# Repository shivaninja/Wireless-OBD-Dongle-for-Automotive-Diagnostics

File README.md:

# Wireless OBD Dongle for Automotive Diagnostics

A custom ESP32-based wireless OBD-II dongle designed to interface with a vehicle's diagnostic port and provide a hardware platform for automotive data acquisition and diagnostics.

This repository currently contains the **KiCad hardware design**: the schematic, PCB layout, supporting symbol/footprint libraries, and 3D component models.

## Project overview

The board is built around an **ESP32-WROOM-32E** module and a **TCAN332 CAN transceiver**. The OBD-II connector provides the vehicle-side interface, while the ESP32 provides the processing and wireless-capable platform.

The design also includes a vehicle-input power conversion stage, USB connectivity for development/programming, user push-buttons, and status LEDs.

> **Repository scope:** The uploaded project contains hardware design files. It does not currently include ESP32 firmware, a mobile application, or a PC diagnostic application. Therefore, software features and supported OBD-II diagnostic parameters depend on firmware and host software that are developed separately.

## Main hardware

| Component / circuit | Purpose |
|---|---|
| ESP32-WROOM-32E | Main microcontroller and wireless-capable processing module |
| TCAN332 | CAN bus physical-layer transceiver |
| C-OBD-II-16M | OBD-II vehicle connector |
| TPS62162DSG | Step-down DC/DC regulator in the power supply section |
| CH340C | USB-to-UART interface |
| USB-C receptacle | USB connection for development / serial communication |
| USBLC6-4SC6 | USB line protection |
| PESD2CANFD24V-T | CAN bus transient/ESD protection |
| SS8050 | NPN transistor used in the supporting circuitry |
| LEDs and push-buttons | Board indication and user input |

Refer to the schematic for the exact wiring, component values, and pin assignments.

## Hardware design

### Schematic

The schematic contains the ESP32 section, CAN transceiver and protection, OBD-II connector, power regulation, USB-to-UART interface, and supporting user-interface circuitry.

### PCB layout

The PCB design includes front- and back-copper routing.

**Front copper**

**Back copper**

### 3D board views

## How the hardware is intended to work

1. The dongle plugs into the vehicle's OBD-II diagnostic connector.
2. The power-supply stage converts the vehicle-side input to a regulated supply for the board.
3. The ESP32 acts as the main controller.
4. The TCAN332 interfaces the controller's CAN signals with the vehicle CAN bus at the physical layer.
5. The ESP32 can use its wireless capabilities to communicate with a separate diagnostic client once suitable firmware and client software are implemented.

The CAN transceiver is the physical-layer interface; OBD-II request/response handling, CAN message processing, wireless data transport, and diagnostic display require software.

## Repository contents

```text
.
├── ESP-CAN.kicad_sch          # KiCad schematic
├── ESP-CAN.kicad_pcb          # KiCad PCB layout
├── ESP-CAN.kicad_pro          # KiCad project settings
├── Pictures/                  # Schematic, PCB, 3D and design-check images
├── C-OBD-II-16M/              # OBD-II connector symbol, footprint and 3D model
├── TCAN332-3D-Model/          # CAN transceiver 3D model
├── TPS62162DSGR-3D-Model/     # Regulator 3D model
├── USB-3d-Model/              # USB connector 3D model
├── fp-lib-table               # KiCad footprint library table
└── sym-lib-table              # KiCad symbol library table
```

## Opening the design

1. Install [KiCad](https://www.kicad.org/).
2. Clone or download this repository.
3. Open `ESP-CAN.kicad_pro` in KiCad.
4. Open the schematic (`ESP-CAN.kicad_sch`) or PCB editor (`ESP-CAN.kicad_pcb`) to inspect the design.
5. Keep the supporting model and library folders in their repository-relative locations so KiCad can resolve the referenced assets.

If KiCad reports a missing library or 3D model, check the project library tables and the paths configured in the symbol/footprint settings.

## Safety and testing notes

- Vehicle electrical systems can expose the circuit to transients, reverse-polarity events, and other conditions beyond ordinary low-voltage bench electronics.
- Verify the input-voltage range, regulator ratings, protection-device ratings, connector pinout, clearances, and grounding before connecting the board to a vehicle.
- Validate the assembled board with a current-limited bench supply before vehicle testing.
- Confirm the CAN wiring and bus configuration for the target vehicle. Do not assume every vehicle exposes the same CAN network on the same OBD-II pins.
- This hardware design alone does not guarantee compatibility with every vehicle or implement any specific diagnostic service.

## Current project status

- [x] KiCad schematic included
- [x] KiCad PCB layout included
- [x] Supporting component libraries and 3D models included
- [x] PCB and 3D design images included
- [ ] ESP32 firmware included in this repository
- [ ] OBD-II diagnostic protocol implementation included
- [ ] Wireless diagnostic client / application included
- [ ] Hardware validation results and supported-vehicle testing documented

Update the checklist as the firmware, application, and test results are added.

## Contributing

Suggestions, design reviews, and improvements are welcome. When proposing hardware changes, include the relevant schematic/PCB updates and note any changes to component ratings, pin assignments, or board dimensions.

## License

No license file was included in as of now.

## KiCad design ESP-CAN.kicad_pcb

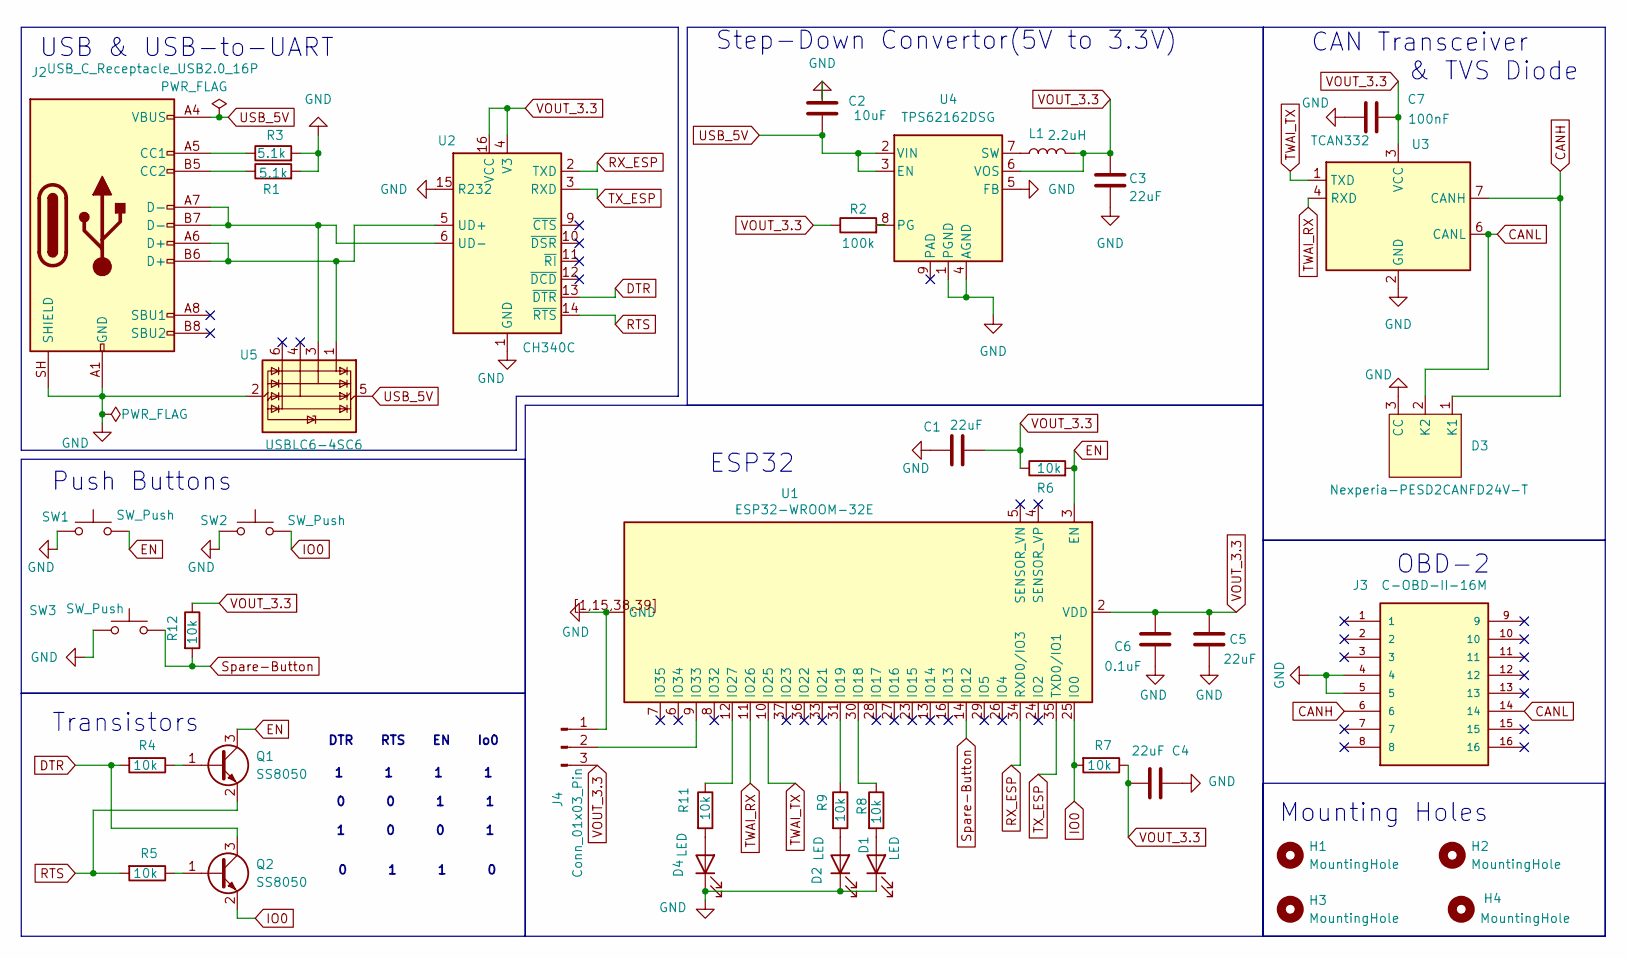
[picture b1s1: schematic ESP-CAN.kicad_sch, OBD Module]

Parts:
C1, C3, C4, C5: 22uF; C_1206_3216Metric_Pad1.33x1.80mm_HandSolder
C2: 10uF; C_0805_2012Metric_Pad1.18x1.45mm_HandSolder
C6: 0.1uF; C_0805_2012Metric_Pad1.18x1.45mm_HandSolder
C7: 100nF; C_0805_2012Metric_Pad1.18x1.45mm_HandSolder
D1, D2, D4: LED; LED_0805_2012Metric_Pad1.15x1.40mm_HandSolder
D3: Nexperia-PESD2CANFD24V-T; SOT-23
H1, H2, H3, H4: MountingHole; MountingHole_2.2mm_M2
J2: USB_C_Receptacle_USB2.0_16P; USB_C_Receptacle_HRO_TYPE-C-31-M-12
J3: C-OBD-II-16M; COMTECH_C-OBD-II-16M; PARTREV A
J4: Conn_01x03_Pin; PinHeader_1x03_P2.54mm_Vertical
L1: 2.2uH; L_0805_2012Metric_Pad1.05x1.20mm_HandSolder
Q1, Q2: SS8050; SOT-23
R1, R3: 5.1k; R_0805_2012Metric_Pad1.20x1.40mm_HandSolder
R2: 100k; R_0805_2012Metric_Pad1.20x1.40mm_HandSolder
R4, R5, R6, R7, R8, R9, R11, R12: 10k; R_0805_2012Metric_Pad1.20x1.40mm_HandSolder
SW1, SW2, SW3: SW_Push; SW_Push_1P1T_NO_CK_KSC6xxJ
U1: ESP32-WROOM-32E
U2: CH340C; SOIC-16_3.9x9.9mm_P1.27mm
U3: TCAN332; SOIC127P599X175-8N
U4: TPS62162DSG; Texas_DSG0008A_WSON-8-1EP_2x2mm_P0.5mm_EP0.9x1.6mm_ThermalV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
U5: USBLC6-4SC6; SOT-23-6

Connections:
CANH: D3.1 (K1), J3.6, U3.7 (CANH)
CANL: D3.2 (K2), J3.14, U3.6 (CANL)
DTR: Q2.3 (C), R4.2, U2.13 (~DTR)
EN: Q1.3 (C), R6.2, SW1.2, U1.3 (EN)
GND: C1.1, C2.1, C3.2, C4.1, C5.2, C6.2, C7.2, D1.1 (K), D2.1 (K), D3.3 (CC), D4.1 (K), J2.A1 (GND), J2.A12 (GND), J2.B1 (GND), J2.B12 (GND), J2.SH (SHIELD), J3.4, J3.5, J4.1, R1.2, R3.2, SW1.1, SW2.1, SW3.1, U1.1 (GND), U1.15 (GND), U1.38 (GND), U1.39 (GND), U1.[1,15,38,39] (GND), U2.1 (GND), U2.15 (R232), U3.2 (GND), U4.1 (PGND), U4.4 (AGND), U4.5 (FB), U5.2 (GND)
IO0: Q2.2 (E), R7.2, SW2.2, U1.25 (IO0)
unnamed: D1.2 (A), R8.2
unnamed: D2.2 (A), R9.2
unnamed: D4.2 (A), R11.2
unnamed: J2.A5 (CC1), R3.1
unnamed: J2.B5 (CC2), R1.1
unnamed: J4.2, U1.9 (IO33)
unnamed: Q1.1 (B), R4.1
unnamed: Q2.1 (B), R5.1
unnamed: R8.1, U1.30 (IO18)
unnamed: R9.1, U1.31 (IO19)
unnamed: R11.1, U1.12 (IO27)
unnamed: J2.A6 (D+), J2.B6 (D+), U2.5 (UD+), U5.1 (I/O1)
unnamed: J2.A7 (D-), J2.B7 (D-), U2.6 (UD-), U5.3 (I/O2)
unnamed: R2.2, U4.8 (PG)
unnamed: L1.1, U4.7 (SW)
RTS: Q1.2 (E), R5.2, U2.14 (~RTS)
RX_ESP: U1.34 (RXD0/IO3), U2.2 (TXD)
Spare-Button: R12.2, SW3.2, U1.14 (IO12)
TWAI_RX: U1.11 (IO26), U3.4 (RXD)
TWAI_TX: U1.10 (IO25), U3.1 (TXD)
TX_ESP: U1.35 (TXD0/IO1), U2.3 (RXD)
USB_5V: C2.2, J2.A4 (VBUS), J2.A9 (VBUS), J2.B4 (VBUS), J2.B9 (VBUS), U4.2 (VIN), U4.3 (EN), U5.5 (VBUS)
VOUT_3.3: C1.2, C3.1, C4.2, C5.1, C6.1, C7.1, J4.3, L1.2, R2.1, R6.1, R7.1, R12.1, U1.2 (VDD), U2.4 (V3), U2.16 (VCC), U3.3 (VCC), U4.6 (VOS)

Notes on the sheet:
Step-Down Convertor(5V to 3.3V)
CAN Transceiver
0 0 1 1
Push Buttons
& TVS Diode
1 1 1 1
OBD-2
0 1 1 0
DTR RTS EN Io0
1 0 0 1
USB & USB-to-UART
Transistors
ESP32
Mounting Holes

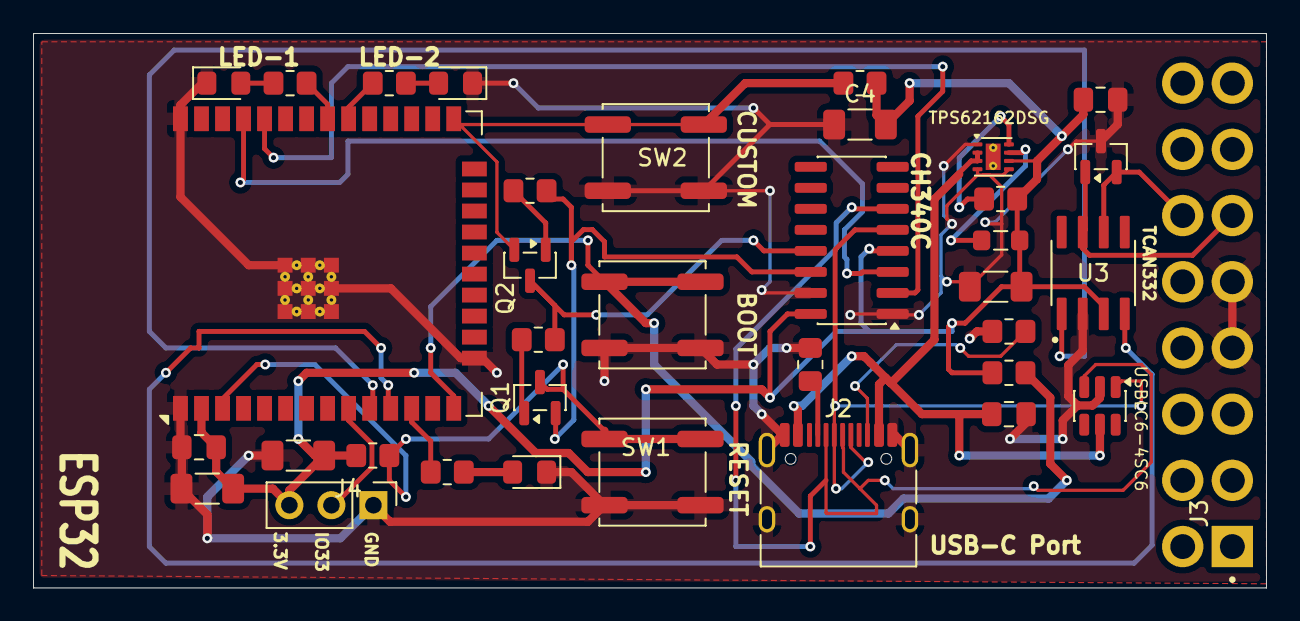
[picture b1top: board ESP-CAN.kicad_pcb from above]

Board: 2 copper layers, 74.5 x 33.5 mm, 36 parts (0 on the bottom side), 29 nets.
